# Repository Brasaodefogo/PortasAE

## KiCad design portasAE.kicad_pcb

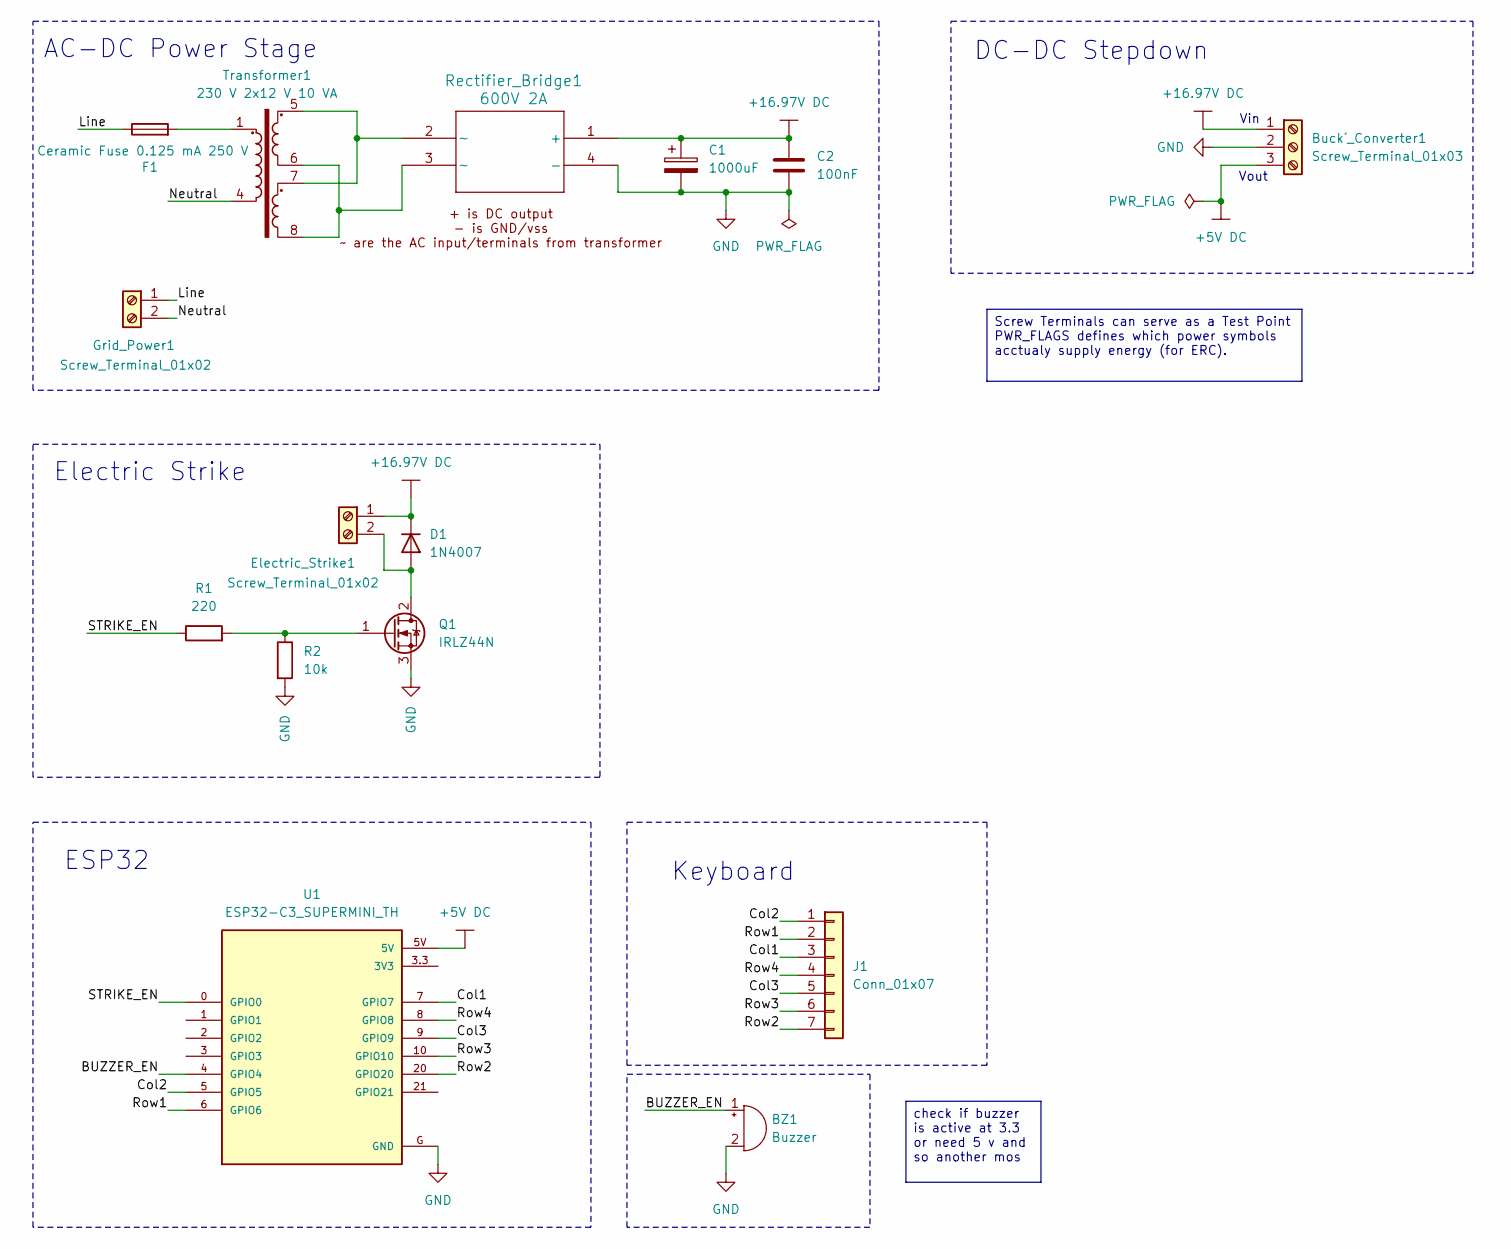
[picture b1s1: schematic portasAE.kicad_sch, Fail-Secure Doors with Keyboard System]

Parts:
BZ1: Buzzer; Buzzer_THT
Buck´_Converter1: Screw_Terminal_01x03; Screw_Terminal_01x03_THT
C1: 1000uF; CP_Radial_D10.0mm_P5.00mm
C2: 100nF; C_Disc_D3.0mm_W1.6mm_P2.50mm
D1: 1N4007; D_DO-41_SOD81_P10.16mm_Horizontal
Electric_Strike1: Screw_Terminal_01x02; Screw_Terminal_01x02_THT
F1: Ceramic Fuse 0.125 mA 250 V; Fuse_Holder_THT
Grid_Power1: Screw_Terminal_01x02; Screw_Terminal_01x02_THT
J1: Conn_01x07; PinHeader_1x07_P2.54mm_Vertical
Q1: IRLZ44N; TO-220-3_Vertical
R1: 220; R_axiaxl_THT_pitch_6,8mm_hole_0,46
R2: 10k; R_axiaxl_THT_pitch_6,8mm_hole_0,46
Rectifier_Bridge1: 600V 2A; Rectifier_Bridge_THT
Transformer1: 230 V 2x12 V 10 VA; Transformer_Breve_TEZ-22x24
U1: ESP32-C3_SUPERMINI_TH; MODULE_ESP32-C3_SUPERMINI_TH

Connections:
+5V DC: Buck´_Converter1.3, U1.5V
+16.97V DC: Buck´_Converter1.1, C1.1, C2.1, D1.1 (K), Electric_Strike1.1, Rectifier_Bridge1.1 (+)
/BUZZER_EN: BZ1.1 (+), U1.4 (GPIO4)
/Col1: J1.3, U1.7 (GPIO7)
/Col2: J1.1, U1.5 (GPIO5)
/Col3: J1.5, U1.9 (GPIO9)
/Line: F1.1, Grid_Power1.1
/Neutral: Grid_Power1.2, Transformer1.4
/Row1: J1.2, U1.6 (GPIO6)
/Row2: J1.7, U1.20 (GPIO20)
/Row3: J1.6, U1.10 (GPIO10)
/Row4: J1.4, U1.8 (GPIO8)
/STRIKE_EN: R1.1, U1.0 (GPIO0)
GND: BZ1.2 (-), Buck´_Converter1.2, C1.2, C2.2, Q1.3 (S), R2.2, Rectifier_Bridge1.4 (-), U1.G (GND)
unnamed: D1.2 (A), Electric_Strike1.2, Q1.2 (D)
unnamed: F1.2, Transformer1.1
unnamed: Q1.1 (G), R1.2, R2.1
unnamed: Rectifier_Bridge1.2 (∼), Transformer1.5, Transformer1.7
unnamed: Rectifier_Bridge1.3 (∼), Transformer1.6, Transformer1.8

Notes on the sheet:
Vout
Electric Strike
ESP32
Vin
Keyboard
DC-DC Stepdown
AC-DC Power Stage
Screw Terminals can serve as a Test Point PWR_FLAGS defines which power symbols acctualy supply energy (for ERC).
check if buzzer is active at 3.3 or need 5 v and so another mos

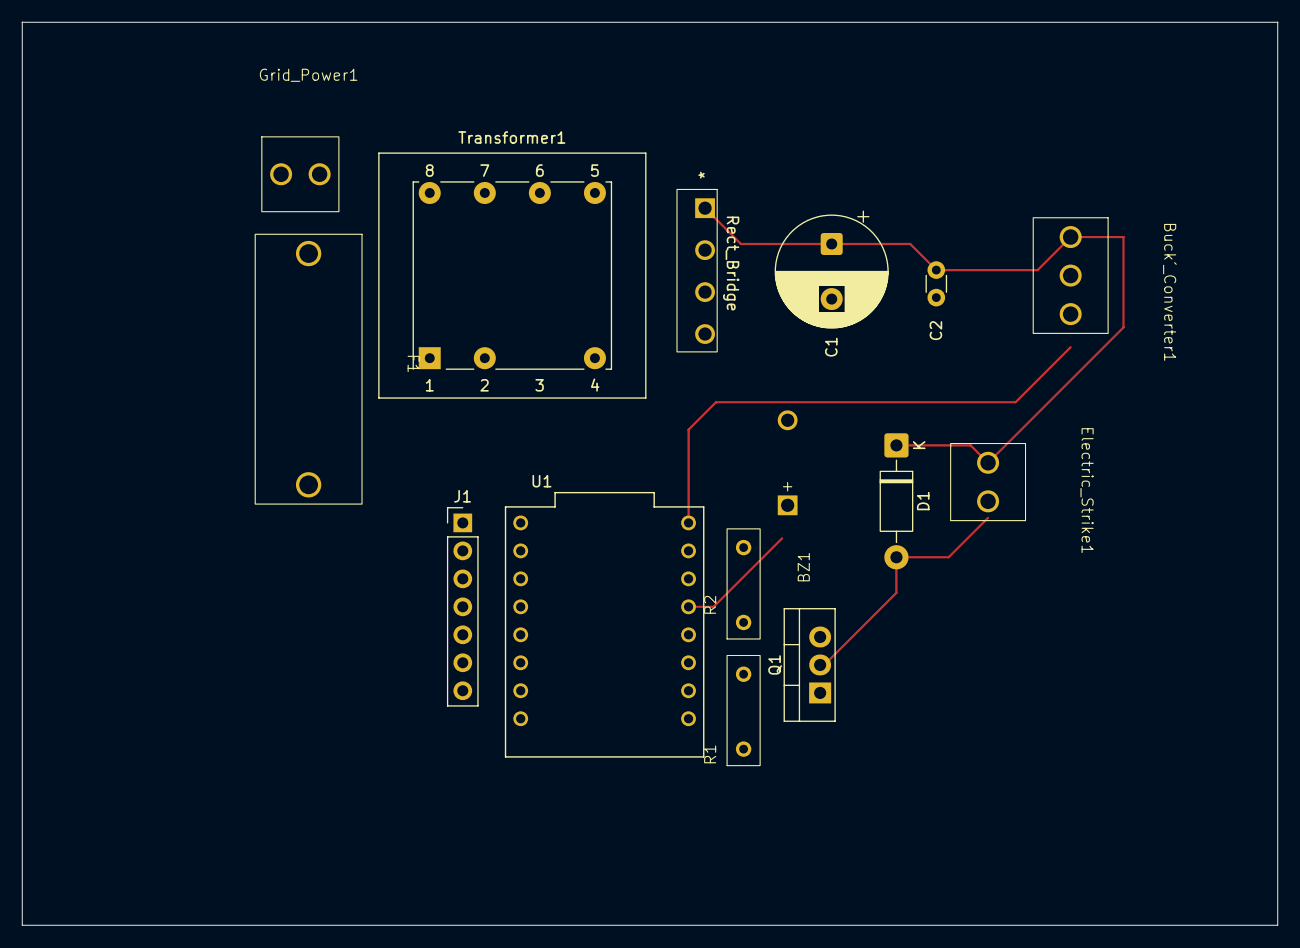
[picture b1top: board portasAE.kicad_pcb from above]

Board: 2 copper layers, 114.0 x 82.0 mm, 15 parts (0 on the bottom side), 19 nets.
